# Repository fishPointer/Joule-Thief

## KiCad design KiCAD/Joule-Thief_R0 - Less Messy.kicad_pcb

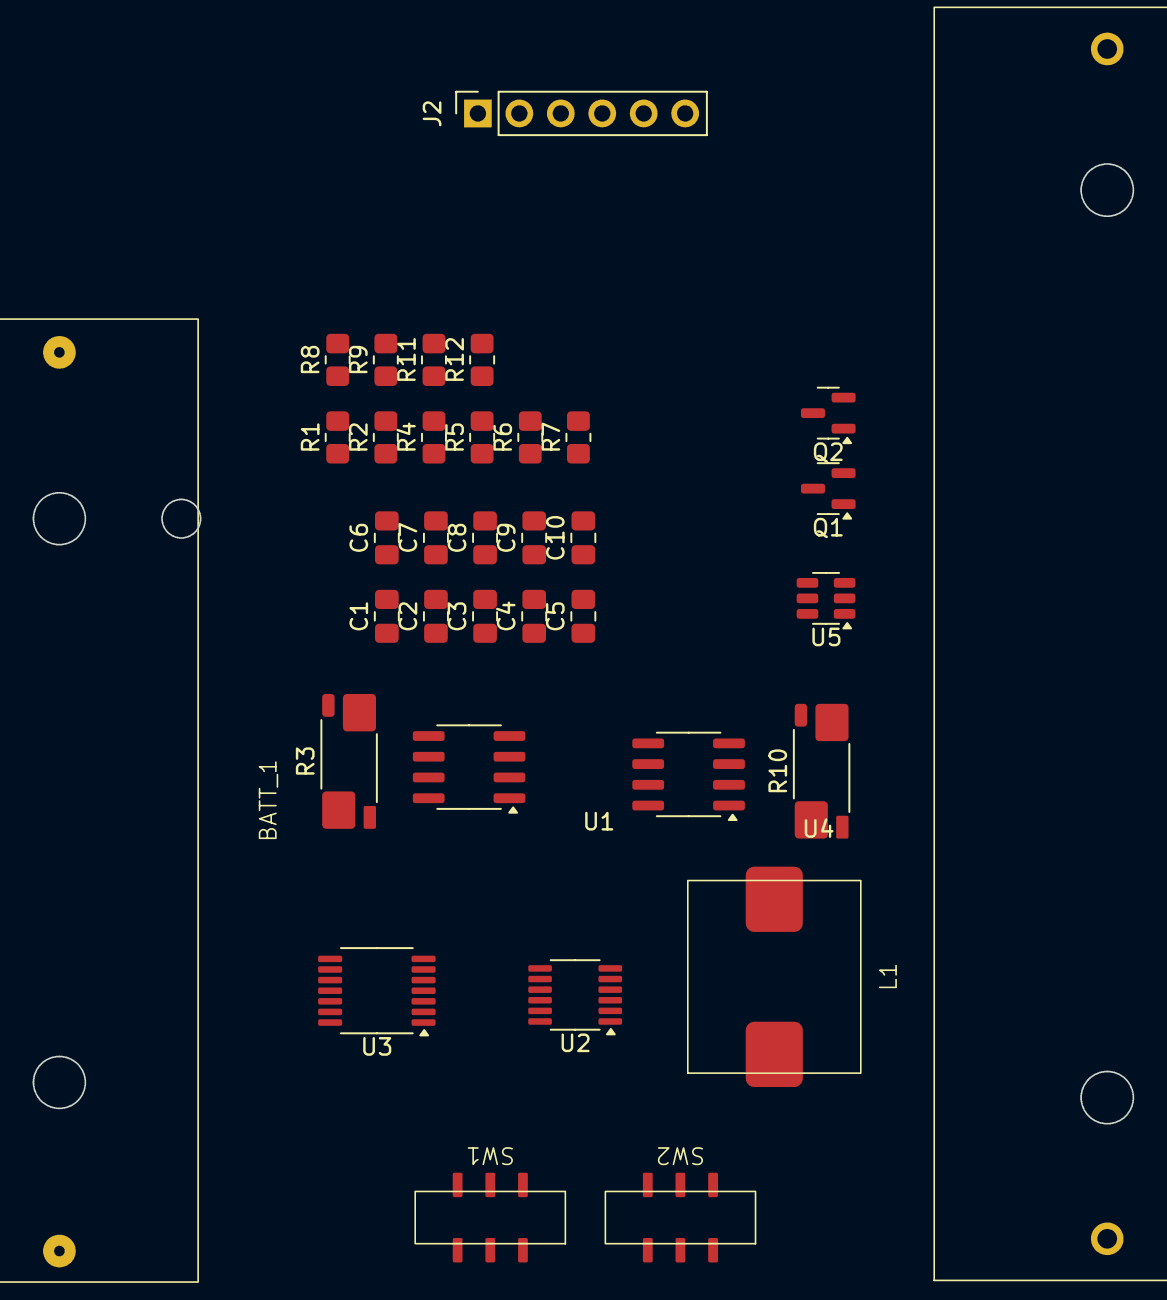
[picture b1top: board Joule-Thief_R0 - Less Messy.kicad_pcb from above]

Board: 2 copper layers, 35 parts (0 on the bottom side), 29 nets, no tracks yet.

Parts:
BATT_1: Alkaline AA; AA_Cell_Clip
BT1: Battery_Cell; 18650_Cell_Clip
C1, C2, C6, C8, C9, C10: 0.1u; C_0805_2012Metric_Pad1.18x1.45mm_HandSolder
C3: 100u; C_0805_2012Metric_Pad1.18x1.45mm_HandSolder
C4: 10u; C_0805_2012Metric_Pad1.18x1.45mm_HandSolder
C5: 1u; C_0805_2012Metric_Pad1.18x1.45mm_HandSolder
C7: 4.7u; C_0805_2012Metric_Pad1.18x1.45mm_HandSolder
J2: Conn_01x06_Socket; PinSocket_1x06_P2.54mm_Vertical
L1: 10u; Power_Inductor_101040
Q1, Q2: AO3400A; SOT-23
R1, R2, R8, R9: 10; R_0805_2012Metric_Pad1.20x1.40mm_HandSolder
R3, R10: 0.1R; R_Shunt_Vishay_WSK2512_6332Metric_T1.19mm
R4, R5: 4.7k; R_0805_2012Metric_Pad1.20x1.40mm_HandSolder
R6: 910k; R_0805_2012Metric_Pad1.20x1.40mm_HandSolder
R7: 220k; R_0805_2012Metric_Pad1.20x1.40mm_HandSolder
R11: 100; R_0805_2012Metric_Pad1.20x1.40mm_HandSolder
R12: 1k; R_0805_2012Metric_Pad1.20x1.40mm_HandSolder
SW1, SW2: SW_SPST; SMD_DPST_Switch
U1, U4: INA219AxD; SOIC-8_3.9x4.9mm_P1.27mm
U2: LTC3105xMS; MSOP-12_3x4.039mm_P0.65mm
U3: AD5280; TSSOP-14_4.4x5mm_P0.65mm
U5: DW01A; SOT-23-6

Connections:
+ALK: BATT_1.1 (+), R3.1
GND: BATT_1.2 (-), C1.2, C3.1, C4.2, C5.2, C6.2, C7.2, C8.2, J2.2, Q1.2 (S), R7.2, R12.1, U1.1 (A1), U1.2 (A0), U1.6 (GND), U2.3 (FBLDO), U2.6 (GND), U2.7 (GND), U3.3 (B), U3.8 (AD0), U3.9 (AD1), U3.10 (GND), U3.11 (VSS), U4.1 (A1), U4.6 (GND)
LITH: BT1.1 (+), J2.6, R10.4, R11.2
MPPC: U2.5 (MPPC), U3.1 (A), U3.2 (W)
unnamed: BT1.2 (-), C10.2, Q2.2 (S), U5.6 (GND)
unnamed: C2.1, R1.2, R3.2
unnamed: C2.2, R2.2, R3.3
unnamed: C9.1, R8.2, R10.2
unnamed: C9.2, R9.2, R10.3
unnamed: Q1.3 (D), Q2.3 (D)
unnamed: Q1.1 (G), U5.3 (OC)
unnamed: Q2.1 (G), U5.1 (OD)
unnamed: R3.4, SW1.1 (A)
unnamed: C4.1, L1.1, SW1.2 (B), U2.8 (VIN)
unnamed: R10.1, SW2.2 (B)
unnamed: R1.1, U1.8 (IN+)
unnamed: R2.1, U1.7 (IN-)
unnamed: C5.1, U2.12 (AUX)
unnamed: R6.2, R7.1, U2.1 (FB)
unnamed: C7.1, U2.2 (LDO)
unnamed: L1.2, U2.9 (SWITCH)
unnamed: R8.1, U4.8 (IN+)
unnamed: R9.1, U4.7 (IN-)
unnamed: R12.2, U5.2 (CS)
unnamed: C10.1, R11.1, U5.5 (VCC)
SCL: J2.4, R4.2, U1.4 (SCL), U3.6 (SCL), U4.4 (SCL)
SDA: J2.3, R5.2, U1.3 (SDA), U3.7 (SDA), U4.3 (SDA)
SHDN: J2.5, U2.4 (~SHDN)
V5+: C1.1, C3.2, C6.1, C8.1, J2.1, R4.1, R5.1, R6.1, SW2.1 (A), U1.5 (VS), U2.11 (VOUT), U3.4 (VDD), U3.13 (VLOG), U4.2 (A0), U4.5 (VS)
